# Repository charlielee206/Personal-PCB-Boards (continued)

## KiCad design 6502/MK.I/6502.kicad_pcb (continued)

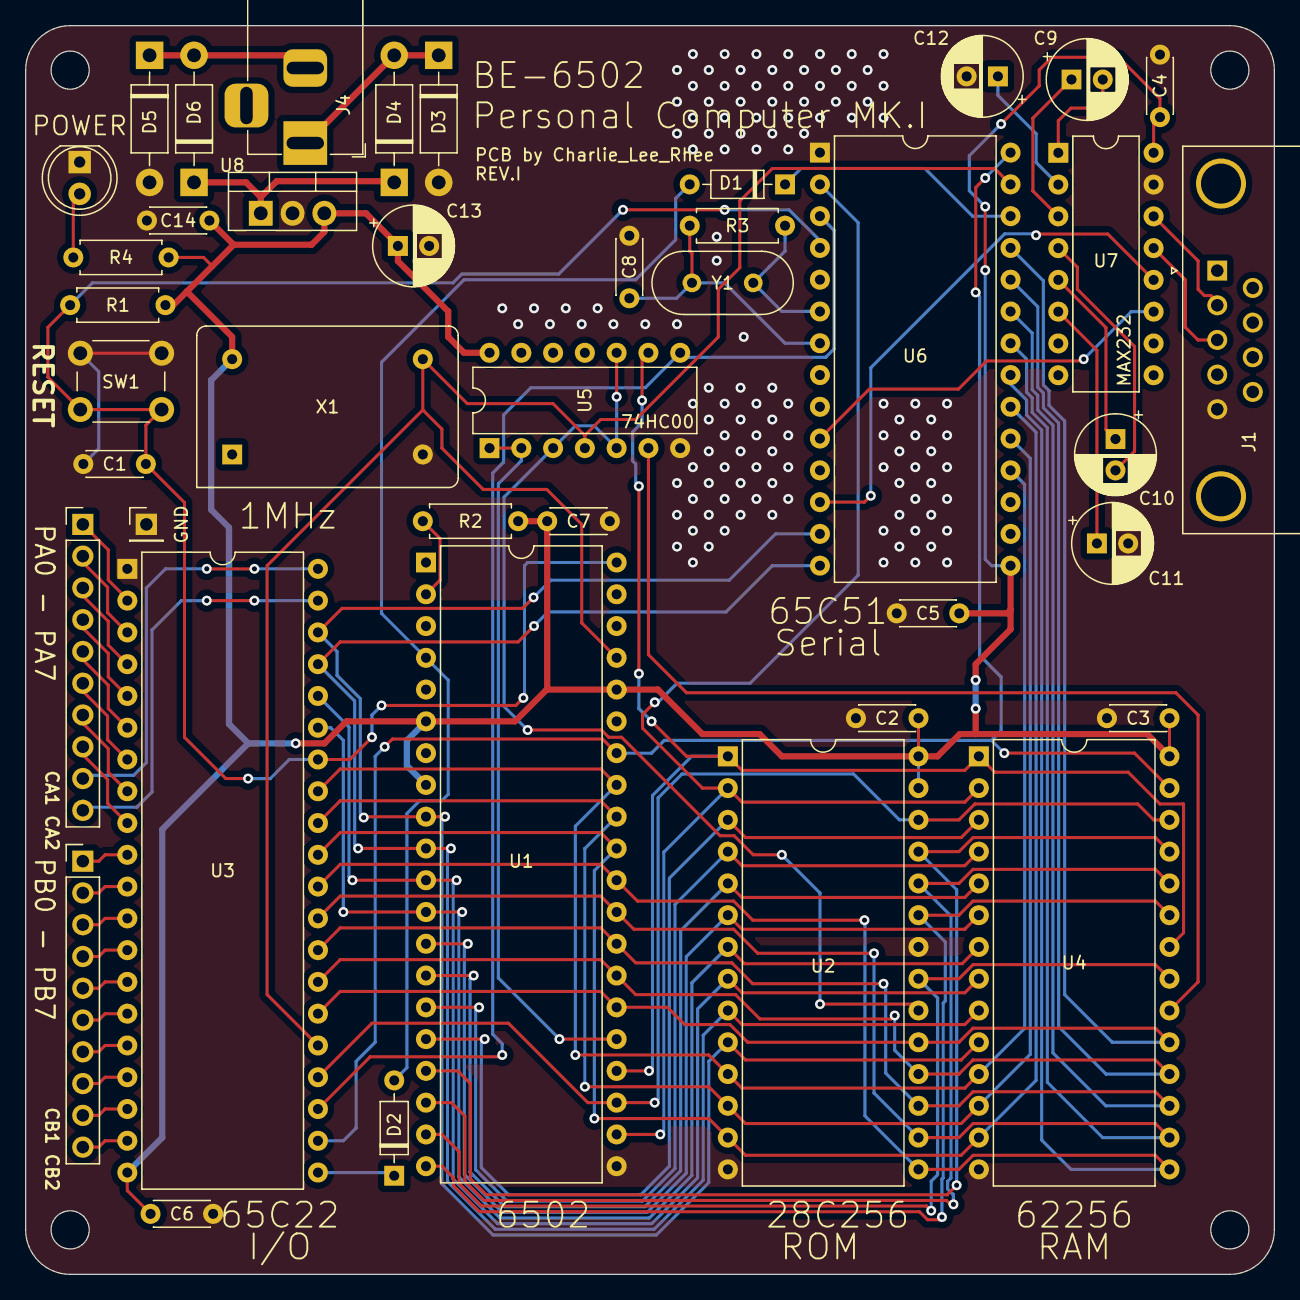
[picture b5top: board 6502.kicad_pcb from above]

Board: 2 copper layers, 99.8 x 99.8 mm, 41 parts (0 on the bottom side), 72 nets.

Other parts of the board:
GND: Screw_Terminal_01x01; PinHeader_1x01_P2.54mm_Vertical

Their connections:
GND: GND.1; also elsewhere on the board

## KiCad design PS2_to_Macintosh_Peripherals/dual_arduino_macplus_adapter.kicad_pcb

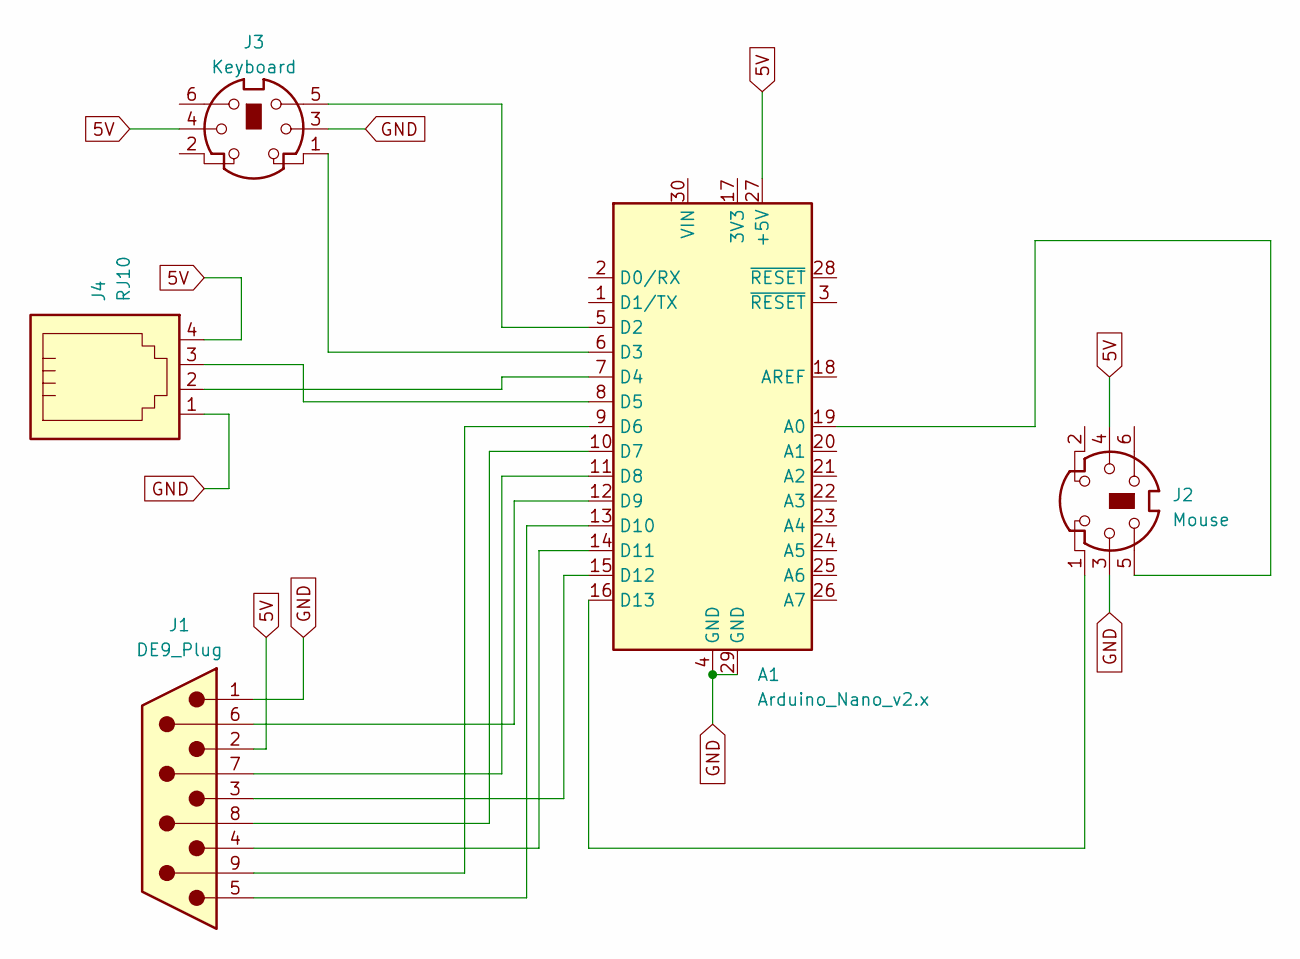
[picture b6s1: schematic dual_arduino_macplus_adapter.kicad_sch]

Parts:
A1: Arduino_Nano_v2.x; Arduino_Nano
J1: DE9_Plug; DSUB-9_Female_Horizontal_P2.77x2.84mm_EdgePinOffset4.94mm_H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
J2: Mouse; Connector_Mini-DIN_Female_6Pin_2rows
J3: Keyboard; Connector_Mini-DIN_Female_6Pin_2rows
J4: RJ10; RJ14_Connfly_DS1133-S4_Horizontal

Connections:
5V: A1.27 (+5V), J1.2, J2.4, J3.4, J4.4
GND: A1.4 (GND), A1.29 (GND), J1.1, J2.3, J3.3, J4.1
unnamed: A1.19 (A0), J2.5
unnamed: A1.5 (D2), J3.5
unnamed: A1.6 (D3), J3.1
unnamed: A1.7 (D4), J4.2
unnamed: A1.8 (D5), J4.3
unnamed: A1.9 (D6), J1.9
unnamed: A1.10 (D7), J1.8
unnamed: A1.11 (D8), J1.7
unnamed: A1.12 (D9), J1.6
unnamed: A1.13 (D10), J1.5
unnamed: A1.14 (D11), J1.4
unnamed: A1.15 (D12), J1.3
unnamed: A1.16 (D13), J2.1

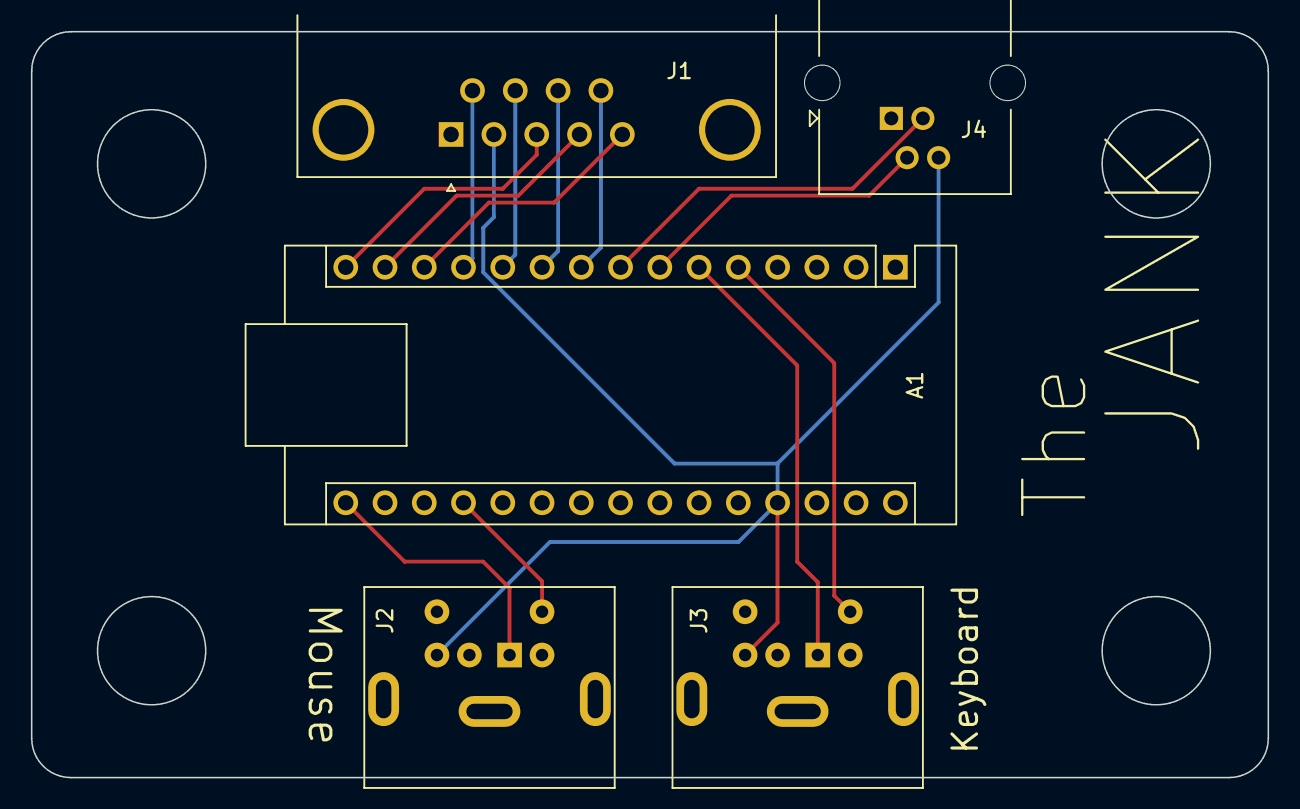
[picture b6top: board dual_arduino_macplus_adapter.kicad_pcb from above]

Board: 2 copper layers, 80.0 x 48.3 mm, 5 parts (0 on the bottom side), 15 nets.

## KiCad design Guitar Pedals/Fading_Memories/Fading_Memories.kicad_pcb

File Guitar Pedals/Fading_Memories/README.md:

This one is basically a clone of the [2399 Weridbrato](https://www.freestompboxes.org/viewtopic.php?t=30445). </br>
This is only a prototype, will change the circuit in another version.

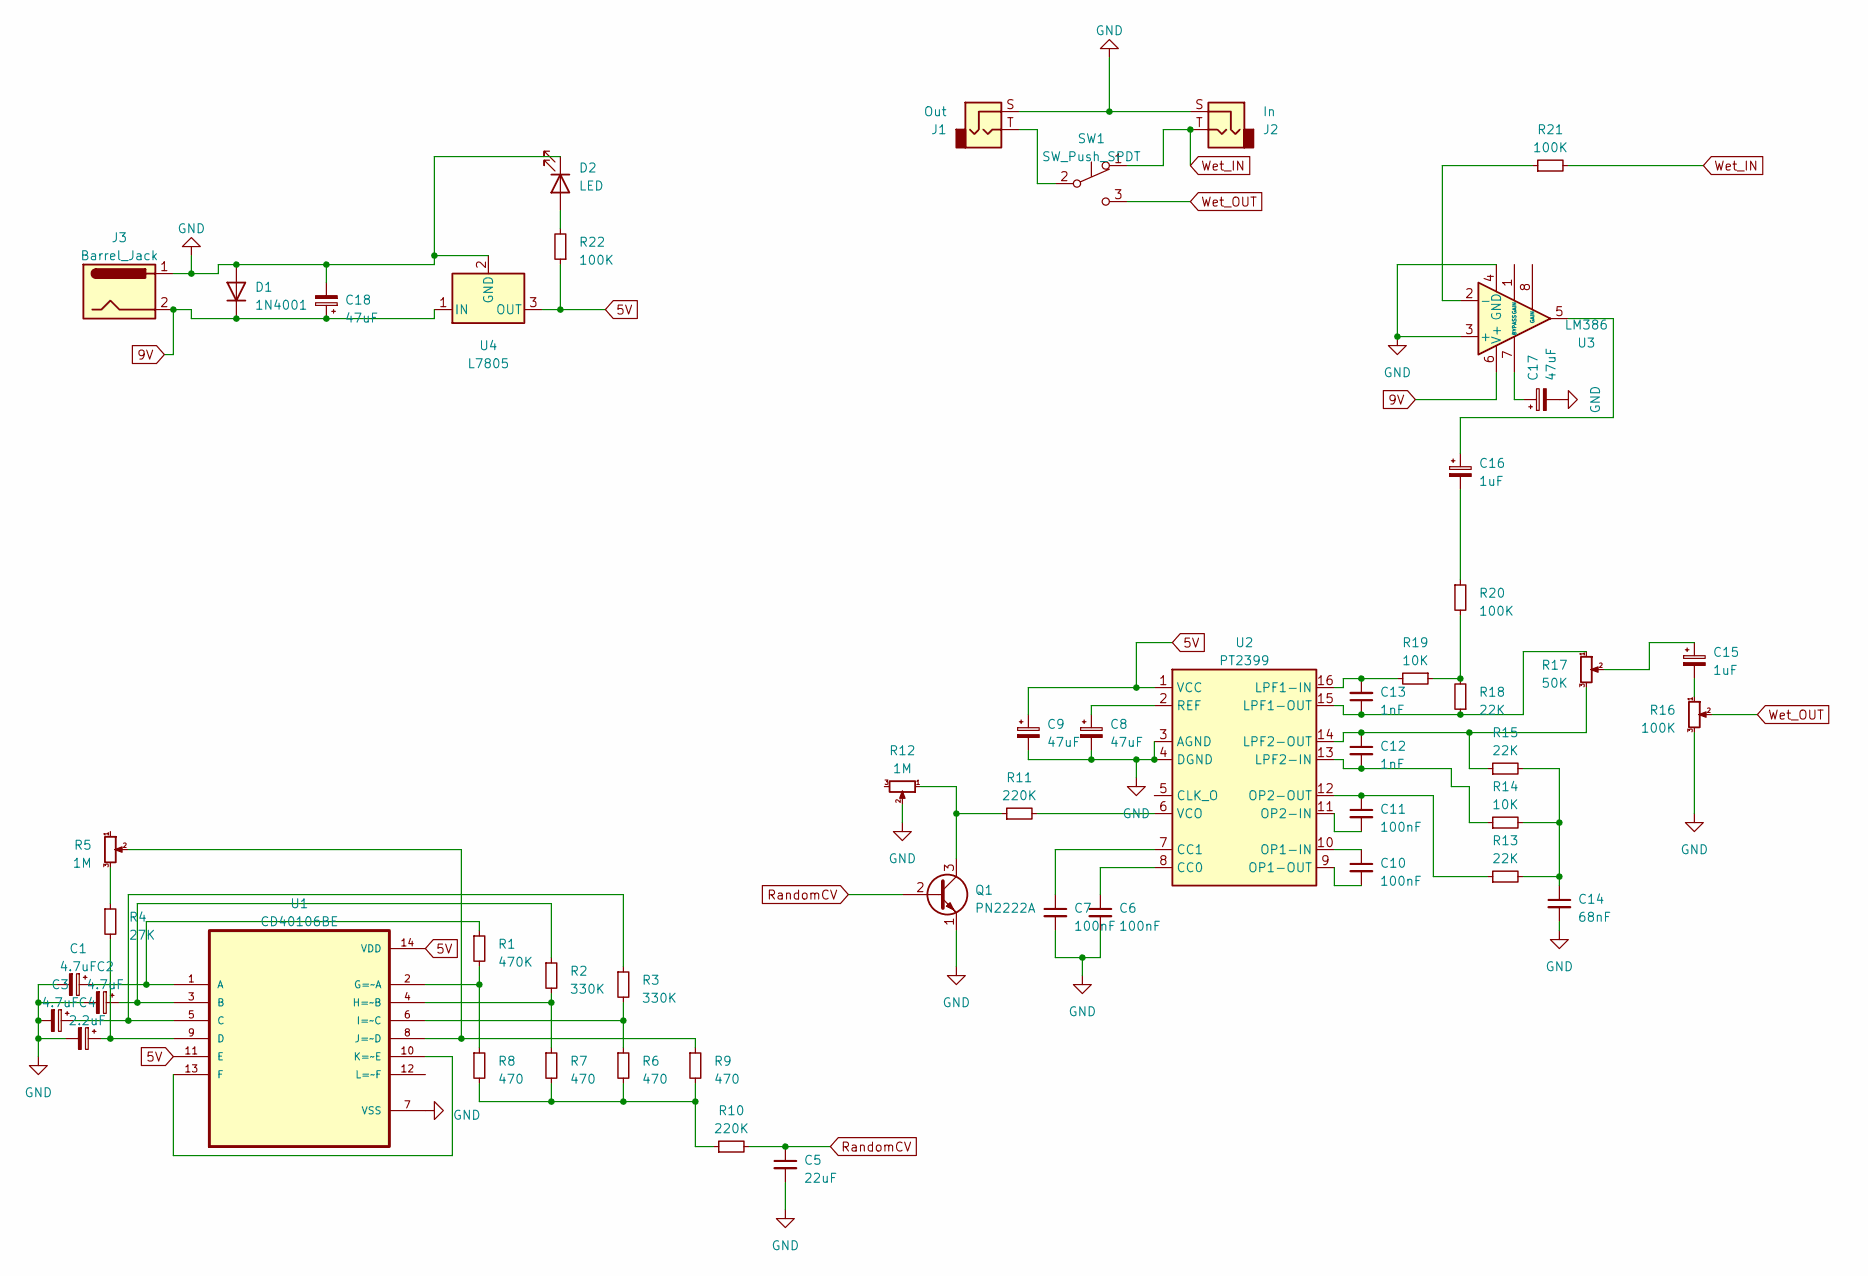
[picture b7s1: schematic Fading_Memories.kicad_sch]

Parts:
C1, C2, C3: 4.7uF; CP_Radial_D5.0mm_P2.50mm
C4: 2.2uF; CP_Radial_D5.0mm_P2.50mm
C5: 22uF; C_Disc_D3.0mm_W1.6mm_P2.50mm
C6, C7, C10, C11: 100nF; C_Disc_D3.0mm_W1.6mm_P2.50mm
C8, C9, C17, C18: 47uF; CP_Radial_D5.0mm_P2.50mm
C12, C13: 1nF; C_Disc_D3.0mm_W1.6mm_P2.50mm
C14: 68nF; C_Disc_D3.0mm_W1.6mm_P2.50mm
C15, C16: 1uF; CP_Radial_D5.0mm_P2.50mm
D1: 1N4001; D_DO-41_SOD81_P10.16mm_Horizontal
D2: LED; LED_D3.0mm
J1: Out; Jack_6.35mm_Neutrik_NMJ4HCD2_Horizontal
J2: In; Jack_6.35mm_Neutrik_NMJ4HCD2_Horizontal
J3: Barrel_Jack; BarrelJack_Horizontal
Q1: PN2222A; TO-92_Inline
R1: 470K; R_Axial_DIN0207_L6.3mm_D2.5mm_P7.62mm_Horizontal
R2, R3: 330K; R_Axial_DIN0207_L6.3mm_D2.5mm_P7.62mm_Horizontal
R4: 27K; R_Axial_DIN0207_L6.3mm_D2.5mm_P7.62mm_Horizontal
R5, R12: 1M; Potentiometer_Omeg_PC16BU_Vertical
R6, R7, R8, R9: 470; R_Axial_DIN0207_L6.3mm_D2.5mm_P7.62mm_Horizontal
R10, R11: 220K; R_Axial_DIN0207_L6.3mm_D2.5mm_P7.62mm_Horizontal
R13, R15, R18: 22K; R_Axial_DIN0207_L6.3mm_D2.5mm_P7.62mm_Horizontal
R14, R19: 10K; R_Axial_DIN0207_L6.3mm_D2.5mm_P7.62mm_Horizontal
R16: 100K; Potentiometer_Omeg_PC16BU_Vertical
R17: 50K; Potentiometer_Omeg_PC16BU_Vertical
R20, R21, R22: 100K; R_Axial_DIN0207_L6.3mm_D2.5mm_P7.62mm_Horizontal
SW1: SW_Push_SPDT; PinHeader_1x03_P2.54mm_Vertical
U1: CD40106BE; DIP-14_W7.62mm
U2: PT2399; DIP-16_W7.62mm
U3: LM386; DIP-8_W7.62mm
U4: L7805; TO-220-3_Vertical

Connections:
5V: C9.1, R22.1, U1.11 (E), U1.14 (VDD), U2.1 (VCC), U4.3 (OUT)
9V: C18.1, D1.1 (K), J3.2, U3.6 (V+), U4.1 (IN)
GND: C1.2, C2.2, C3.2, C4.2, C5.2, C6.2, C7.2, C8.2, C9.2, C14.2, C17.2, C18.2, D1.2 (A), D2.1 (K), J1.S, J2.S, J3.1, Q1.1 (E), R12.2, R16.3, U1.7 (VSS), U2.3 (AGND), U2.4 (DGND), U3.3 (+), U3.4 (GND), U4.2 (GND)
unnamed: C14.1, R13.2, R14.2, R15.2
unnamed: C15.1, R17.2
unnamed: C15.2, R16.1
unnamed: C16.1, U3.5
unnamed: C16.2, R20.1
unnamed: D2.2 (A), R22.2
unnamed: Q1.3 (C), R11.1, R12.1
unnamed: R4.1, R5.3
unnamed: R6.2, R7.2, R8.2, R9.2, R10.1
unnamed: R18.2, R19.1, R20.2
unnamed: J1.T, SW1.2 (B)
unnamed: C1.1, R1.1, U1.1 (A)
unnamed: C2.1, R2.1, U1.3 (B)
unnamed: C3.1, R3.1, U1.5 (C)
unnamed: C4.1, R4.2, U1.9 (D)
unnamed: U1.10 (K=~E), U1.13 (F)
unnamed: R1.2, R8.1, U1.2 (G=~A)
unnamed: R2.2, R7.1, U1.4 (H=~B)
unnamed: R3.2, R6.1, U1.6 (I=~C)
unnamed: R5.2, R9.1, U1.8 (J=~D)
unnamed: C6.1, U2.8 (CC0)
unnamed: C7.1, U2.7 (CC1)
unnamed: C13.2, R19.2, U2.16 (LPF1-IN)
unnamed: C13.1, R17.1, R18.1, U2.15 (LPF1-OUT)
unnamed: C12.2, R14.1, U2.13 (LPF2-IN)
unnamed: C12.1, R15.1, R17.3, U2.14 (LPF2-OUT)
unnamed: C10.1, U2.10 (OP1-IN)
unnamed: C10.2, U2.9 (OP1-OUT)
unnamed: C11.2, U2.11 (OP2-IN)
unnamed: C11.1, R13.1, U2.12 (OP2-OUT)
unnamed: C8.1, U2.2 (REF)
unnamed: R11.2, U2.6 (VCO)
unnamed: R21.1, U3.2 (-)
unnamed: C17.1, U3.7 (BYPASS)
RandomCV: C5.1, Q1.2 (B), R10.2
Wet_IN: J2.T, R21.2, SW1.1 (A)
Wet_OUT: R16.2, SW1.3 (C)

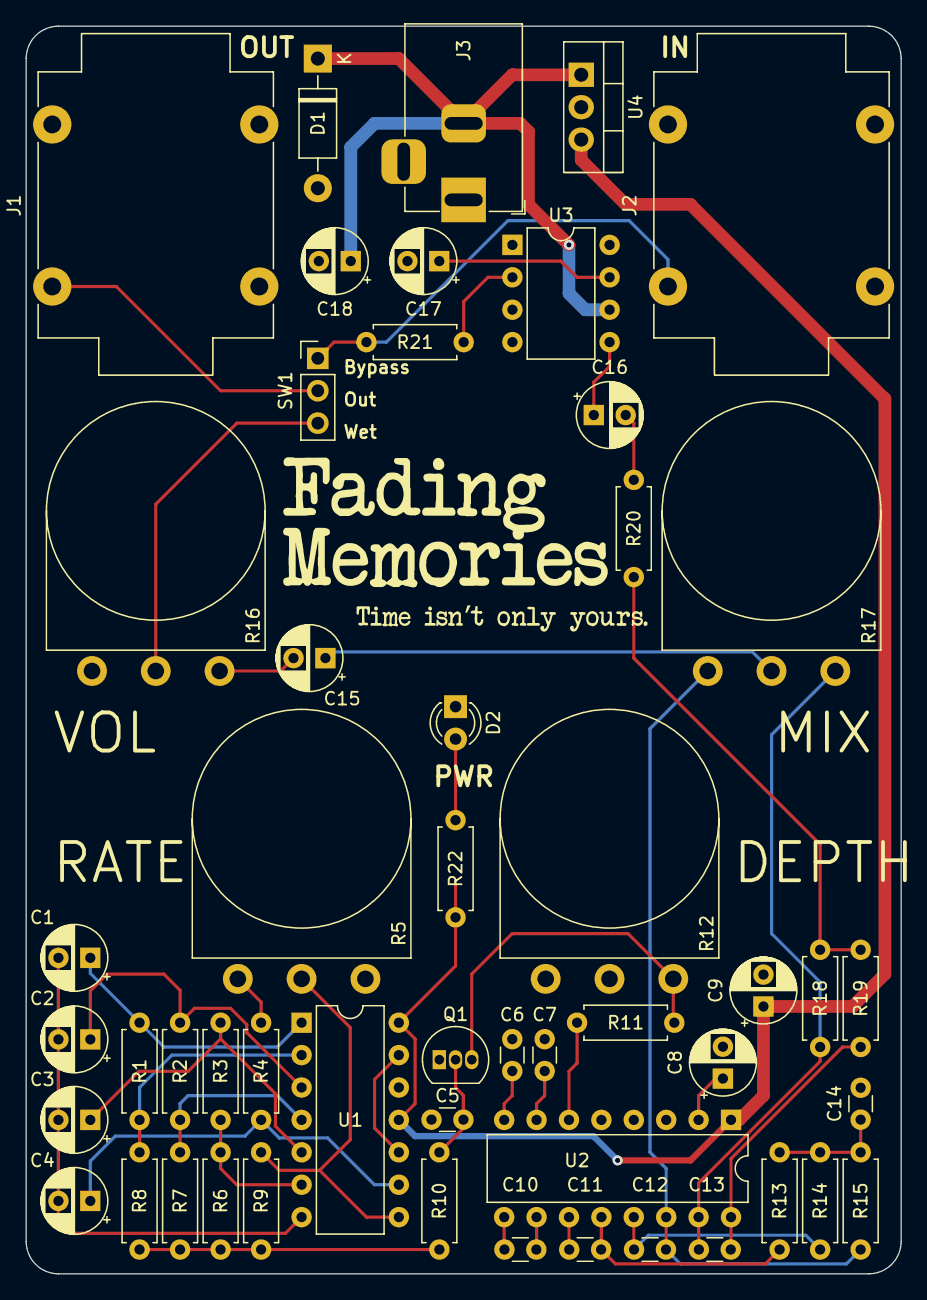
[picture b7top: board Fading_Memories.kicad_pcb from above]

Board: 2 copper layers, 68.6 x 97.8 mm, 51 parts (0 on the bottom side), 40 nets.

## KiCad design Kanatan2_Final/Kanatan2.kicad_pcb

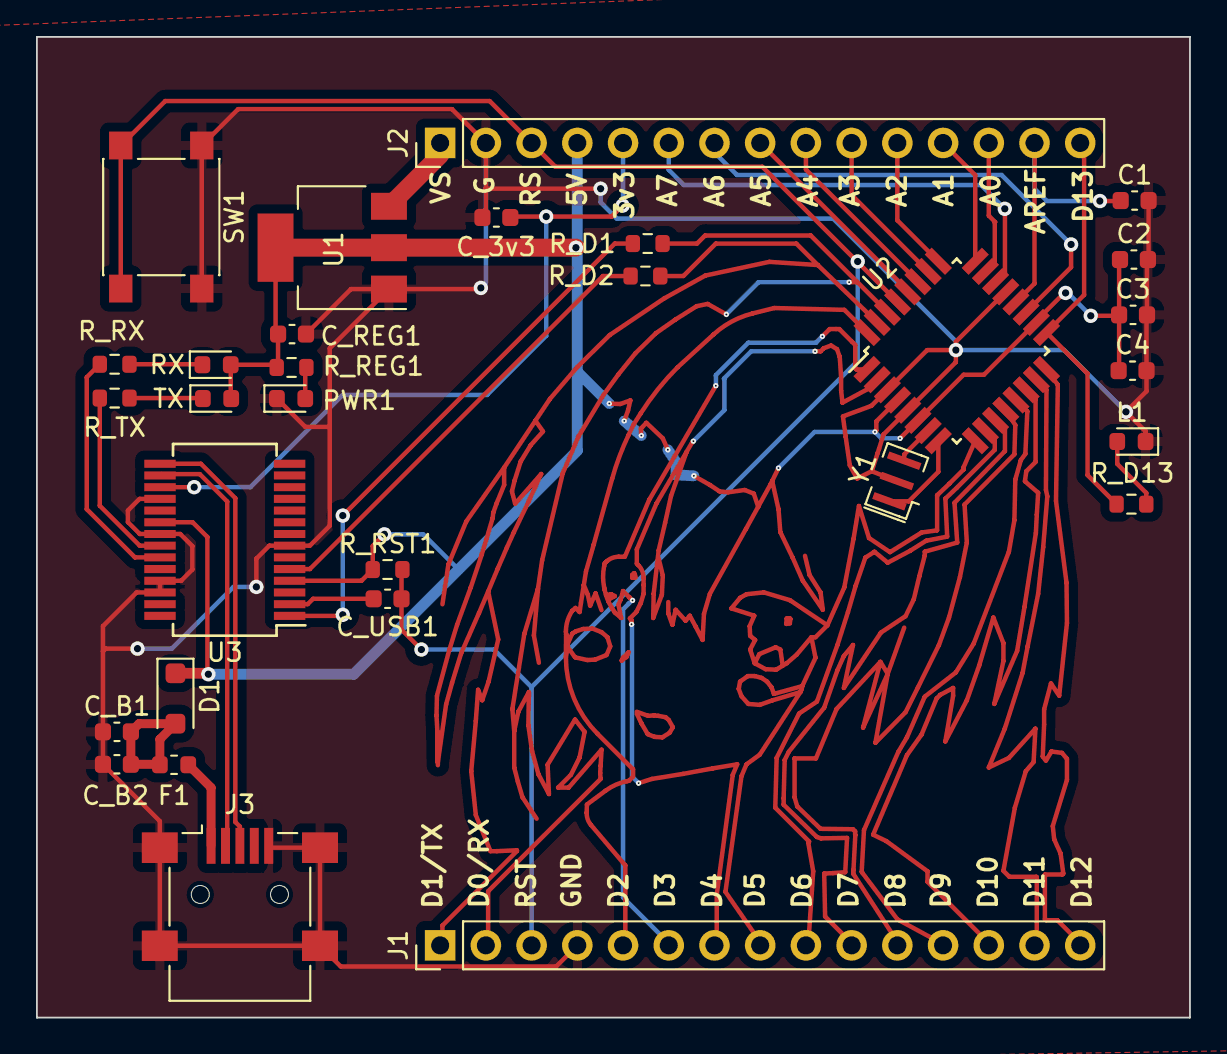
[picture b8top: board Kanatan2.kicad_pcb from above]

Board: 2 copper layers, 64.1 x 54.5 mm, 30 parts (0 on the bottom side), 43 nets.

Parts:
C1: 100nF; C_0603_1608Metric
C2, C4: 1uF; C_0603_1608Metric
C3: 4.7uF; C_0603_1608Metric
C_3v3: 100nF; C_0603_1608Metric
C_B1: 4.7uF; C_0603_1608Metric
C_B2: 100nF; C_0603_1608Metric
C_REG1: 1uF; C_0603_1608Metric
C_USB1: 100nF; C_0603_1608Metric
D1: D; D_SOD-123F
F1: Fuse; Fuse_0603_1608Metric
J1, J2: Conn_01x15; PinHeader_1x15_P2.54mm_Vertical
J3: USB_B_Mini; USB_Mini-B_Lumberg_2486_01_Horizontal
L1: LED_BUILTIN; LED_0603_1608Metric
PWR1: LED_PWR; LED_0603_1608Metric
RX: LED_RX; LED_0603_1608Metric
R_D1, R_D2, R_D13: 1K; R_0603_1608Metric
R_REG1: 1K; R_0603_1608Metric
R_RST1: 1K; R_0603_1608Metric
R_RX: 1K; R_0603_1608Metric
R_TX: 1K; R_0603_1608Metric
SW1: SW_DIP_x01; SW_Push_1P1T_NO_6x6mm_H9.5mm
TX: LED_TX; LED_0603_1608Metric
U1: AMS1117; SOT-223-3_TabPin2
U2: ATmega328P-A; TQFP-32_7x7mm_P0.8mm
U3: FT232RL; SSOP-28_5.3x10.2mm_P0.65mm
Y1: CSTCE16M0V53-R0; Resonator_SMD_Murata_CSTxExxV-3Pin_3.0x1.1mm

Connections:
+3.3V: C_3v3.2, J2.5, U3.17 (3V3OUT)
+5V: C2.1, C3.1, C4.1, C_REG1.1, D1.1 (K), J2.4, RX.2 (A), R_REG1.2, R_RST1.1, TX.2 (A), U1.2 (VO), U2.4 (VCC), U2.6 (VCC), U2.18 (AVCC), U3.4 (VCCIO), U3.20 (VCC)
/A0: J2.13, U2.23 (PC0)
/A1: J2.12, U2.24 (PC1)
/A2: J2.11, U2.25 (PC2)
/A3: J2.10, U2.26 (PC3)
/A4: J2.9, U2.27 (PC4)
/A5: J2.8, U2.28 (PC5)
/A6: J2.7, U2.19 (ADC6)
/A7: J2.6, U2.22 (ADC7)
/AREF: C1.1, J2.14, U2.20 (AREF)
/D0/RX: J1.2, R_D1.2, U2.30 (PD0)
/D1/TX: J1.1, R_D2.2, U2.31 (PD1)
/D2: J1.5, U2.32 (PD2)
/D3: J1.6, U2.1 (PD3)
/D4: J1.7, U2.2 (PD4)
/D5: J1.8, U2.9 (PD5)
/D6: J1.9, U2.10 (PD6)
/D7: J1.10, U2.11 (PD7)
/D8: J1.11, U2.12 (PB0)
/D9: J1.12, U2.13 (PB1)
/D10: J1.13, U2.14 (PB2)
/D11/MOSI: J1.14, U2.15 (PB3)
/D12/MISO: J1.15, U2.16 (PB4)
/D13/SCK: J2.15, R_D13.2, U2.17 (PB5)
/RST: C_USB1.2, J1.3, J2.3, R_RST1.2, SW1.2, U2.29 (~RESET/PC6)
/RX: R_D1.1, U3.1 (TXD)
/TX: R_D2.1, U3.5 (RXD)
GND: C1.2, C2.2, C3.2, C4.2, C_3v3.1, C_B1.1, C_B2.1, C_REG1.2, J1.4, J2.2, J3.5 (GND), J3.6 (Shield), L1.1 (K), PWR1.1 (K), SW1.1, U1.1 (ADJ), U2.3 (GND), U2.5 (GND), U2.21 (GND), U3.7 (GND), U3.18 (GND), U3.21 (GND), U3.25 (AGND), U3.26 (TEST), Y1.2
unnamed: J3.3 (D+), U3.15 (USBD+)
unnamed: J3.2 (D-), U3.16 (USBD-)
unnamed: F1.2, J3.1 (VBUS)
unnamed: L1.2 (A), R_D13.1
unnamed: PWR1.2 (A), R_REG1.1
unnamed: RX.1 (K), R_RX.1
unnamed: R_TX.1, TX.1 (K)
unnamed: U2.7 (XTAL1/PB6), Y1.3
unnamed: U2.8 (XTAL2/PB7), Y1.1
unnamed: R_RX.2, U3.23 (CBUS0)
unnamed: R_TX.2, U3.22 (CBUS1)
unnamed: C_USB1.1, U3.2 (DTR)
VBUS: C_B1.2, C_B2.2, D1.2 (A), F1.1
VS: J2.1, U1.3 (VI)

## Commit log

2023-01-20 Add files via upload - KCS-UART-SMD
    Add initial files
2023-01-20 Add files via upload - KCS_UART_THT
2023-01-20 Add filed via upload - PCB_Colour_Swatch
2023-05-24 Added Amane Kanata PCB
2023-06-11 [Bae RNG] Added Files via Upload
2023-06-11 [Bae RNG] Uploaded Code
2024-04-27 {EmptyPedal] Changed wrong wirings
2024-04-29 [PersonalPedalLibraries]Update README.md
2024-10-06 [HoLo_RAT] Fixed TR pinout
